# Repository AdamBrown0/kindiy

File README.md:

# kindiy
A project to repurpose a Kindle 4th Generation Non Touch

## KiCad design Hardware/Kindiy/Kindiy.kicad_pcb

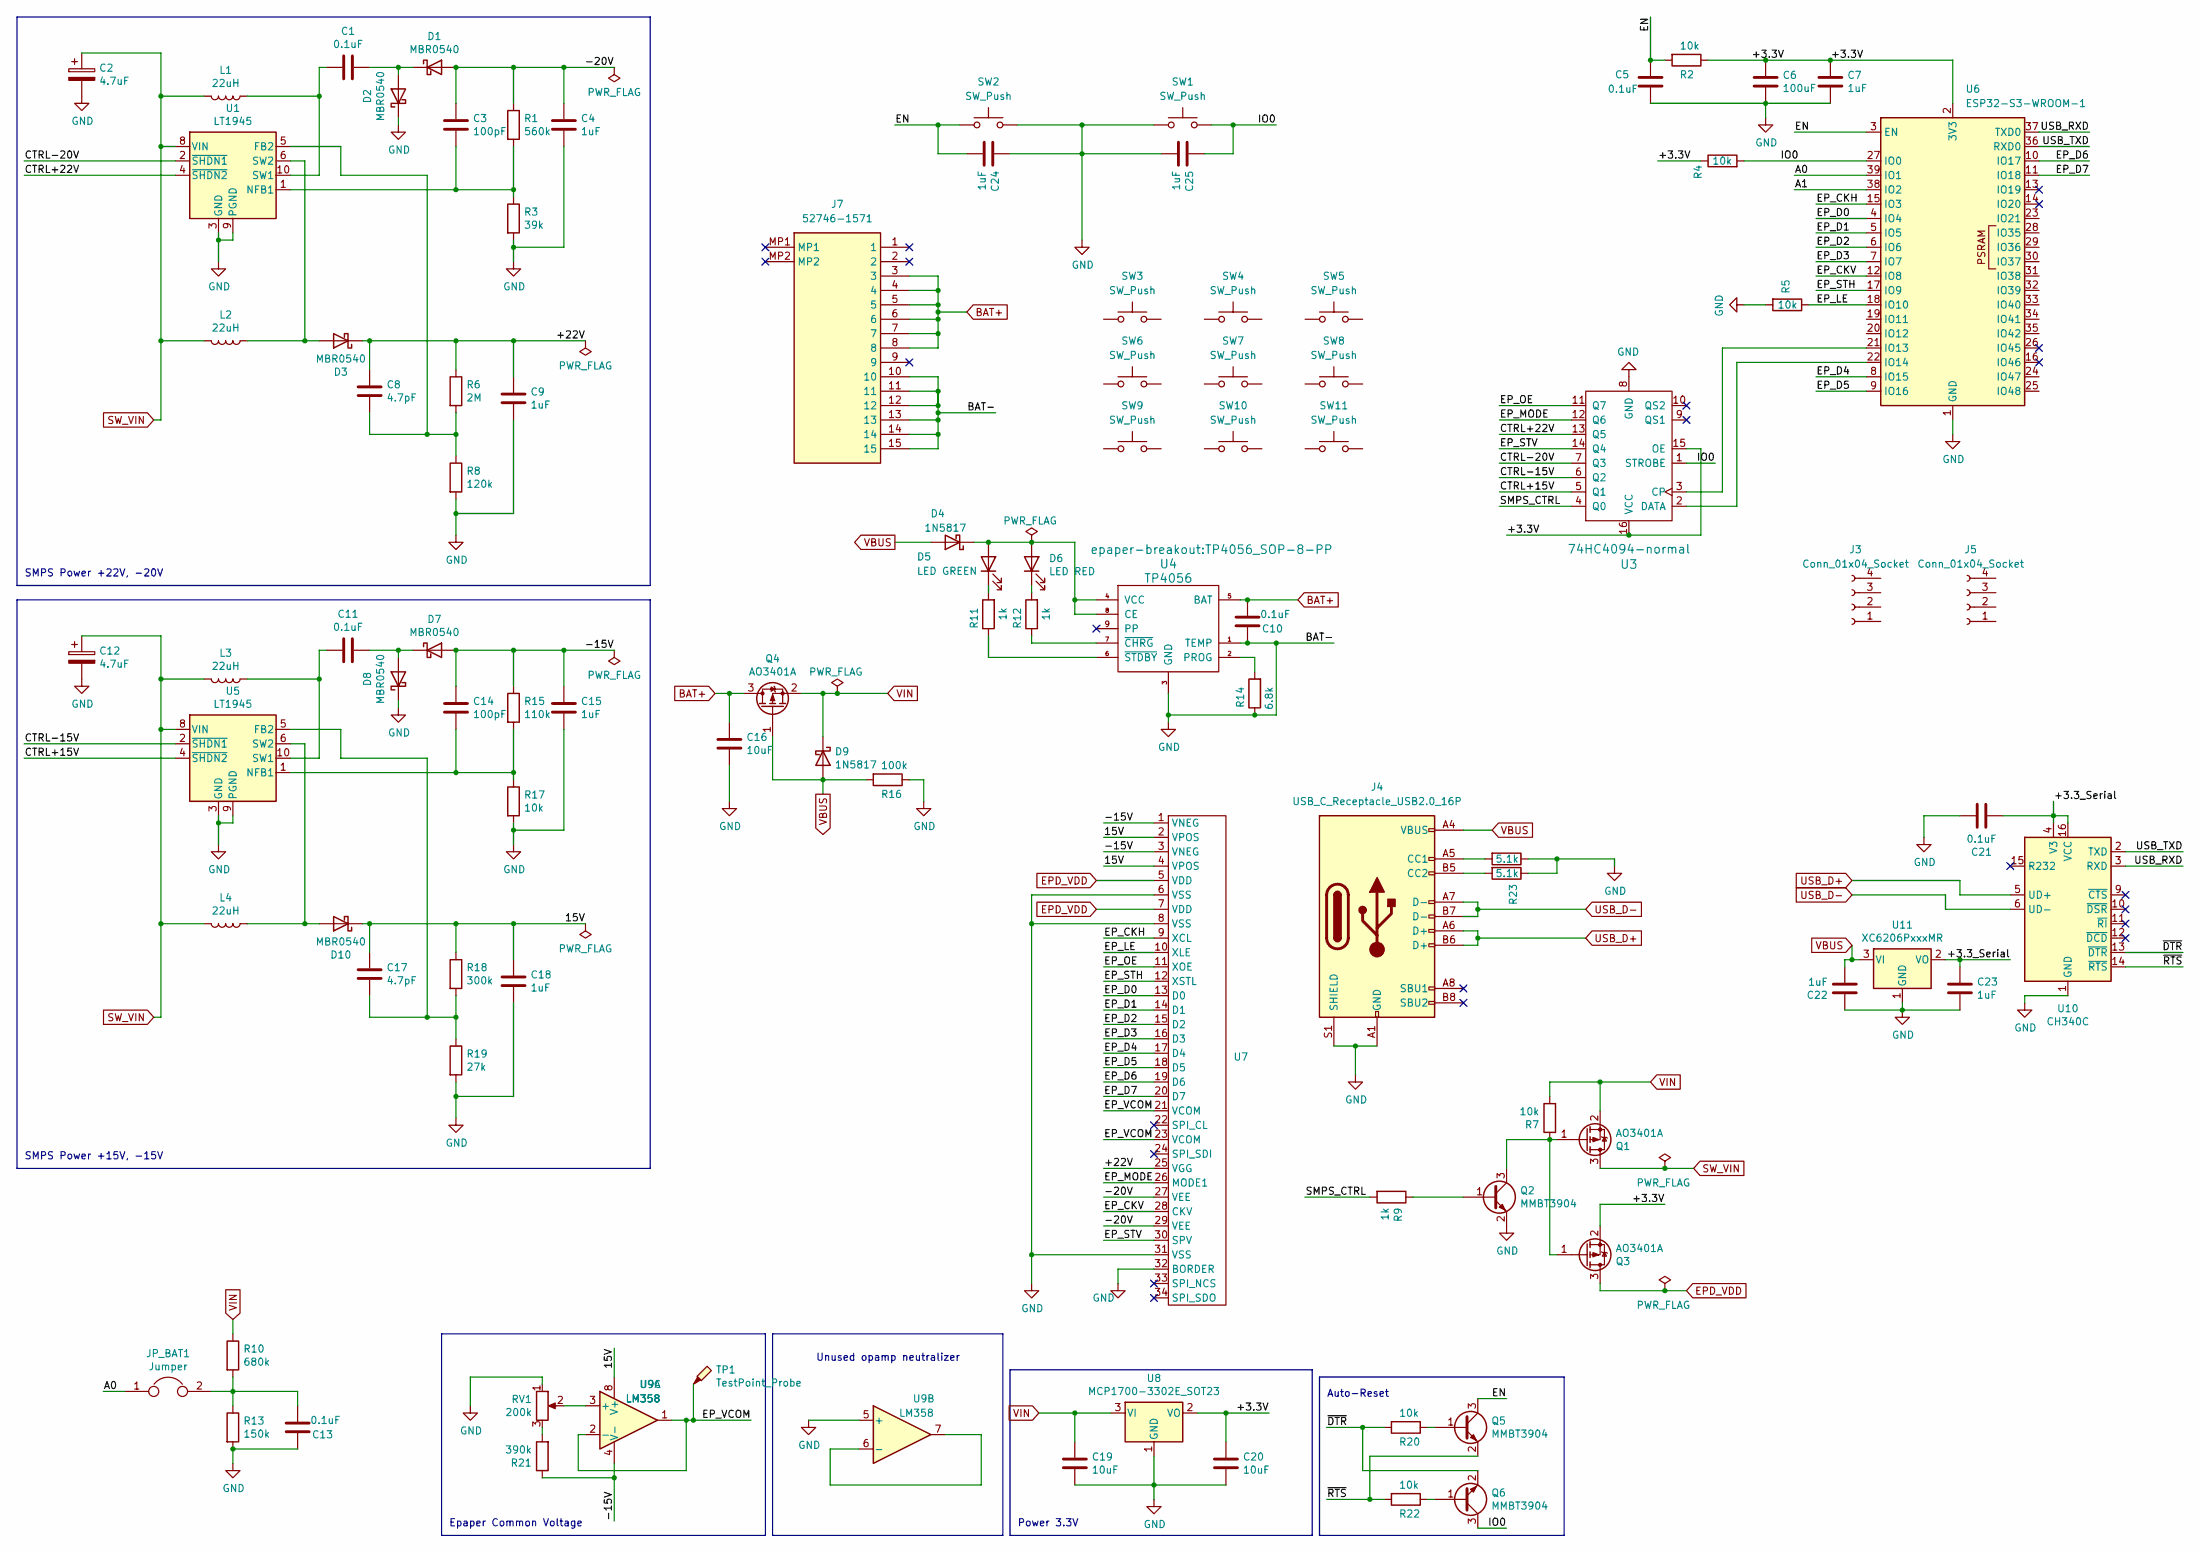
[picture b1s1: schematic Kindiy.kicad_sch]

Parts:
C1, C10, C11, C13, C21: 0.1uF; C_0603_1608Metric; LCSC C14663
C2, C12: 4.7uF; C_0603_1608Metric; LCSC C19666
C3, C14: 100pF; C_0603_1608Metric; LCSC C14858
C4, C7, C9, C15, C18, C22, C23: 1uF; C_0603_1608Metric; LCSC C15849
C5: 0.1uF; C_0603_1608Metric; LCSC C1588
C6: 100uF; CP_EIA-3528-15_AVX-H; LCSC C16133
C8, C17: 4.7pF; C_0603_1608Metric; LCSC C1669
C16, C19, C20: 10uF; C_0603_1608Metric; LCSC C19702
C24, C25: 1uF; CP_EIA-3528-15_AVX-H; LCSC C16133
D1, D2, D3, D7, D8, D10: MBR0540; D_SOD-123; LCSC C21353
D4, D9: 1N5817; D_SOD-123; LCSC C8598
D5: LED GREEN; LED_0805_2012Metric; LCSC C2297
D6: LED RED; LED_0805_2012Metric; LCSC C84256
J3, J5: Conn_01x04_Socket; 5051100492
J4: USB_C_Receptacle_USB2.0_16P; USB_C_Receptacle_G-Switch_GT-USB-7010ASV
J7: 52746-1571; 527461571; Mouser Part Number 538-52746-1571
JP_BAT1: Jumper; SolderJumper-2_P1.3mm_Bridged2Bar_RoundedPad1.0x1.5mm
L1, L2, L3, L4: 22uH; L_6.3x6.3_H3; LCSC C206321
Q1, Q3, Q4: AO3401A; SOT-23; LCSC C15127
Q2, Q5, Q6: MMBT3904; SOT-23; LCSC C20526
R1: 560k; R_0805_2012Metric; LCSC C15785
R2, R4, R5, R7, R17, R20, R22: 10k; R_0805_2012Metric; LCSC C17414
R3: 39k; R_0805_2012Metric; LCSC C25826
R6: 2M; R_0805_2012Metric; LCSC C26112
R8: 120k; R_0805_2012Metric; LCSC C17436
R9, R11, R12: 1k; R_0805_2012Metric; LCSC C17513
R10: 680k; R_0805_2012Metric; LCSC C17797
R13: 150k; R_0805_2012Metric; LCSC C17470
R14: 6.8k; R_0805_2012Metric; LCSC C17772
R15: 110k; R_0805_2012Metric; LCSC C17422
R16: 100k; R_0805_2012Metric; LCSC C17407
R18: 300k; R_0805_2012Metric; LCSC C17616
R19: 27k; R_0805_2012Metric; LCSC C17593
R21: 390k; R_0805_2012Metric; LCSC C17656
R23, R24: 5.1k; R_0805_2012Metric; LCSC C17414
RV1: 200k; EVM3ESX50B25; LCSC C11958
SW1: SW_Push; SW_PUSH_6mm
SW2: SW_Push; 15712621
SW3, SW4, SW5, SW6, SW7, SW8, SW9, SW10, SW11: SW_Push; SW_SPST_SKQG_WithStem
TP1: TestPoint_Probe; TestPoint_Pad_D1.0mm
U1, U5: LT1945; MSOP-10_3x3mm_P0.5mm
U3: 74HC4094-normal; SOIC-16_3.9x9.9mm_P1.27mm; LCSC C5651
U4: TP4056; TP4056_SOP-8-PP; LCSC C16581
U6: ESP32-S3-WROOM-1
U7: TE_3-1734839-4_1x34-1MP_P0.5mm_Horizontal
U8: MCP1700-3302E_SOT23; SOT-23; LCSC C39051
U9: LM358; SOP-8_3.76x4.96mm_P1.27mm
U10: CH340C; SOIC-16_3.9x9.9mm_P1.27mm; LCSC C84681
U11: XC6206PxxxMR; SOT-23; LCSC C5446

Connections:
/15V: C17.2, C18.2, D10.1 (K), R18.1, U7.2 (VPOS), U7.4 (VPOS), U9.8 (V+)
/+3.3V: C6.1, C7.2, C20.2, Q3.2 (S), R2.1, R4.1, U3.15 (OE), U3.16 (VCC), U6.2 (3V3), U8.2 (VO)
/+3.3_Serial: C21.1, C23.2, U10.4 (V3), U10.16 (VCC), U11.2 (VO)
/+22V: C8.2, C9.2, D3.1 (K), R6.1, U7.25 (VGG)
/-15V: C14.2, C15.2, D7.2 (A), R15.1, R21.1, U7.1 (VNEG), U7.3 (VNEG), U9.4 (V-)
/-20V: C3.2, C4.2, D1.2 (A), R1.1, U7.27 (VEE), U7.29 (VEE)
/A0: JP_BAT1.1, U6.39 (IO1)
/A1: U6.38 (IO2)
/CTRL+15V: U3.5 (Q1), U5.4 (~SHDN2)
/CTRL+22V: U1.4 (~SHDN2), U3.13 (Q5)
/CTRL-15V: U3.6 (Q2), U5.2 (~SHDN1)
/CTRL-20V: U1.2 (~SHDN1), U3.7 (Q3)
/EN: C5.1, C24.2, Q5.3 (C), R2.2, SW2.1, U6.3 (EN)
/EP_CKH: U6.15 (IO3), U7.9 (XCL)
/EP_CKV: U6.12 (IO8), U7.28 (CKV)
/EP_D0: U6.4 (IO4), U7.13 (D0)
/EP_D1: U6.5 (IO5), U7.14 (D1)
/EP_D2: U6.6 (IO6), U7.15 (D2)
/EP_D3: U6.7 (IO7), U7.16 (D3)
/EP_D4: U6.8 (IO15), U7.17 (D4)
/EP_D5: U6.9 (IO16), U7.18 (D5)
/EP_D6: U6.10 (IO17), U7.19 (D6)
/EP_D7: U6.11 (IO18), U7.20 (D7)
/EP_LE: R5.1, U6.18 (IO10), U7.10 (XLE)
/EP_MODE: U3.12 (Q6), U7.26 (MODE1)
/EP_OE: U3.11 (Q7), U7.11 (XOE)
/EP_STH: U6.17 (IO9), U7.12 (XSTL)
/EP_STV: U3.14 (Q4), U7.30 (SPV)
/EP_VCOM: TP1.1, U7.21 (VCOM), U7.23 (VCOM), U9.1, U9.2 (-)
/IO0: C25.1, Q6.3 (C), R4.2, SW1.2, U3.1 (STROBE), U6.27 (IO0)
/SMPS_CTRL: R9.2, U3.4 (Q0)
/USB_RXD: U6.37 (TXD0), U10.3 (RXD)
/USB_TXD: U6.36 (RXD0), U10.2 (TXD)
/~DTR: Q6.2 (E), R20.2, U10.13 (~DTR)
/~RTS: Q5.2 (E), R22.2, U10.14 (~RTS)
BAT+: C10.2, C16.1, J7.3, J7.4, J7.5, J7.6, J7.7, J7.8, Q4.3 (D), U4.5 (BAT)
EPD_VDD: Q3.3 (D), U7.5 (VDD), U7.7 (VDD)
GND: C2.2, C4.1, C5.2, C6.2, C7.1, C9.1, C10.1, C12.2, C13.1, C15.1, C16.2, C18.1, C19.1, C20.1, C21.2, C22.2, C23.1, C24.1, C25.2, D2.1 (K), D8.1 (K), J4.A1 (GND), J4.A12 (GND), J4.B1 (GND), J4.B12 (GND), J4.S1 (SHIELD), J7.10, J7.11, J7.12, J7.13, J7.14, J7.15, Q2.2 (E), R3.2, R5.2, R8.2, R13.2, R14.1, R16.1, R17.2, R19.2, R23.1, R24.1, RV1.1, SW1.1, SW2.2, U1.3 (GND), U1.7 (PGND), U1.9 (PGND), U3.8 (GND), U4.1 (TEMP), U4.3 (GND), U5.3 (GND), U5.7 (PGND), U5.9 (PGND), U6.1 (GND), U6.40 (GND), U6.41 (GND), U7.6 (VSS), U7.8 (VSS), U7.31 (VSS), U7.32 (BORDER), U8.1 (GND), U9.5 (+), U10.1 (GND), U11.1 (GND)
unnamed: C13.2, JP_BAT1.2, R10.2, R13.1
unnamed: C1.1, D1.1 (K), D2.2 (A)
unnamed: D3.2 (A), L2.1, U1.6 (SW2)
unnamed: D4.1 (K), D5.2 (A), D6.2 (A), U4.4 (VCC), U4.8 (CE)
unnamed: D5.1 (K), R11.2
unnamed: D6.1 (K), R12.2
unnamed: C11.1, D7.1 (K), D8.2 (A)
unnamed: D10.2 (A), L4.1, U5.6 (SW2)
unnamed: J4.A5 (CC1), R24.2
unnamed: J4.B5 (CC2), R23.2
unnamed: Q1.1 (G), Q2.3 (C), Q3.1 (G), R7.1
unnamed: Q2.1 (B), R9.1
unnamed: Q5.1 (B), R20.1
unnamed: Q6.1 (B), R22.1
unnamed: R21.2, RV1.3
unnamed: C8.1, R6.2, R8.1, U1.5 (FB2)
unnamed: C3.1, R1.2, R3.1, U1.1 (NFB1)
unnamed: C1.2, L1.1, U1.10 (SW1)
unnamed: U3.3 (CP), U6.21 (IO13)
unnamed: U3.2 (DATA), U6.22 (IO14)
unnamed: R14.2, U4.2 (PROG)
unnamed: R12.1, U4.7 (~CHRG)
unnamed: R11.1, U4.6 (~STDBY)
unnamed: C17.1, R18.2, R19.1, U5.5 (FB2)
unnamed: C14.1, R15.2, R17.1, U5.1 (NFB1)
unnamed: C11.2, L3.1, U5.10 (SW1)
unnamed: RV1.2, U9.3 (+)
unnamed: U9.6 (-), U9.7
SW_VIN: C2.1, C12.1, L1.2, L2.2, L3.2, L4.2, Q1.3 (D), U1.8 (VIN), U5.8 (VIN)
USB_D+: J4.A6 (D+), J4.B6 (D+), U10.5 (UD+)
USB_D-: J4.A7 (D-), J4.B7 (D-), U10.6 (UD-)
VBUS: C22.1, D4.2 (A), D9.2 (A), J4.A4 (VBUS), J4.A9 (VBUS), J4.B4 (VBUS), J4.B9 (VBUS), Q4.1 (G), R16.2, U11.3 (VI)
VIN: C19.2, D9.1 (K), Q1.2 (S), Q4.2 (S), R7.2, R10.1, U8.3 (VI)

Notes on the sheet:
SMPS Power +15V, -15V
Epaper Common Voltage
SMPS Power +22V, -20V
Auto-Reset
Unused opamp neutralizer
Power 3.3V

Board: 2 copper layers, 95 parts (11 on the bottom side), 65 nets, no tracks yet.

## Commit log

2024-09-19 initial hardware mockup, schedmatic complete no placement
